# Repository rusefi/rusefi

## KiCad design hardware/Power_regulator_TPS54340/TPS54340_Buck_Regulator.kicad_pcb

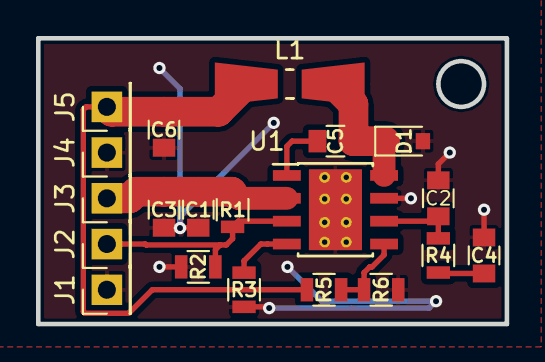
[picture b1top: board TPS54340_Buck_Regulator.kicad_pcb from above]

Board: 2 copper layers, 26.0 x 15.9 mm, 20 parts (0 on the bottom side), 10 nets.

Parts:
C1, C3: 2.2uF; C_0805
C2: 47pF; C_0805
C4: 5600pF; C_0805
C5: 0.1uF; C_0805
C6: 100uF; C_0805
D1: B560C; D_0805
J1, J2, J3, J4, J5: Conn_01x01; Pin_Header_Straight_1x01_Pitch2.54mm
L1: 5.6uH; Resistor_SMDuniversal_0805to1206_HandSoldering
R1: 365k; R_0805
R2: 86k6; R_0805
R3: 162k; R_0805
R4: 11k5; R_0805
R5: 31.6; R_0805
R6: 10.2; R_0805
U1: TPS54340; TI_SO-PowerPAD-8_ThermalVias

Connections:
/BOOT: C5.2, U1.1
/COMP: C2.1, R4.1, U1.6
/EN: J2.1, R1.1, R2.1, U1.3
/FB: R5.2, R6.1, U1.5
/RT/CLK: R3.1, U1.4
/SW: C5.1, D1.1, L1.1, U1.8
/VIN: C1.2, C3.2, J3.1, R1.2, U1.2
/VOUT: C6.1, J5.1, L1.2, R5.1
GND: C1.1, C2.2, C3.1, C4.2, C6.2, D1.2, J1.1, J4.1, R2.2, R3.2, R6.2, U1.7, U1.9
unnamed: C4.1, R4.2

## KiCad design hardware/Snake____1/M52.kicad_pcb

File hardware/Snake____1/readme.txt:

See http://rusefi.com/forum/viewtopic.php?f=3&t=1099 for details

By Snake____1

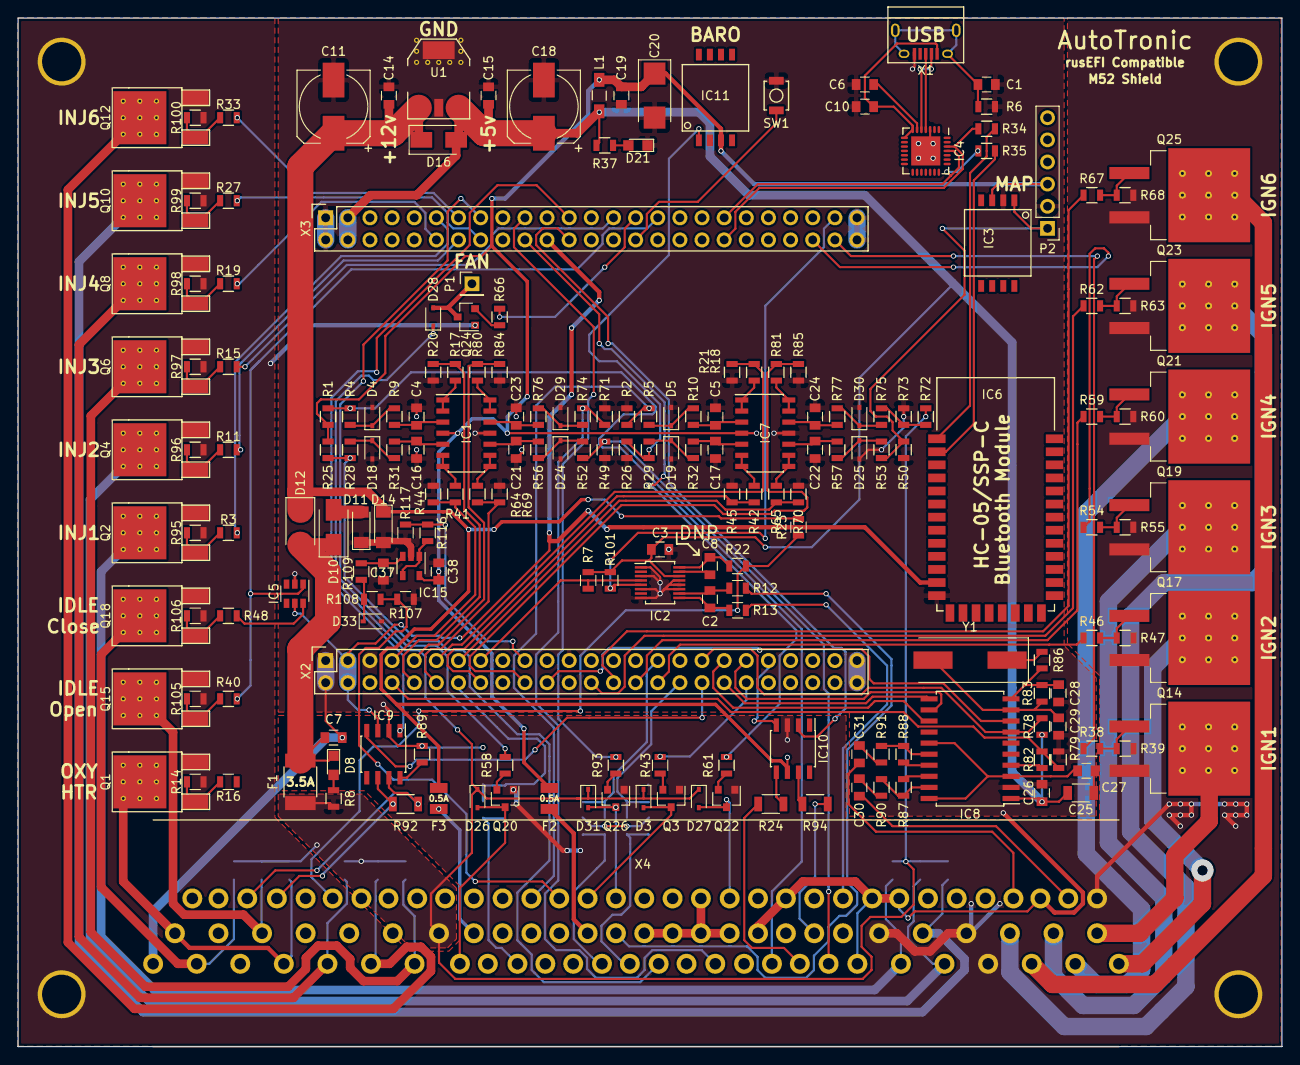
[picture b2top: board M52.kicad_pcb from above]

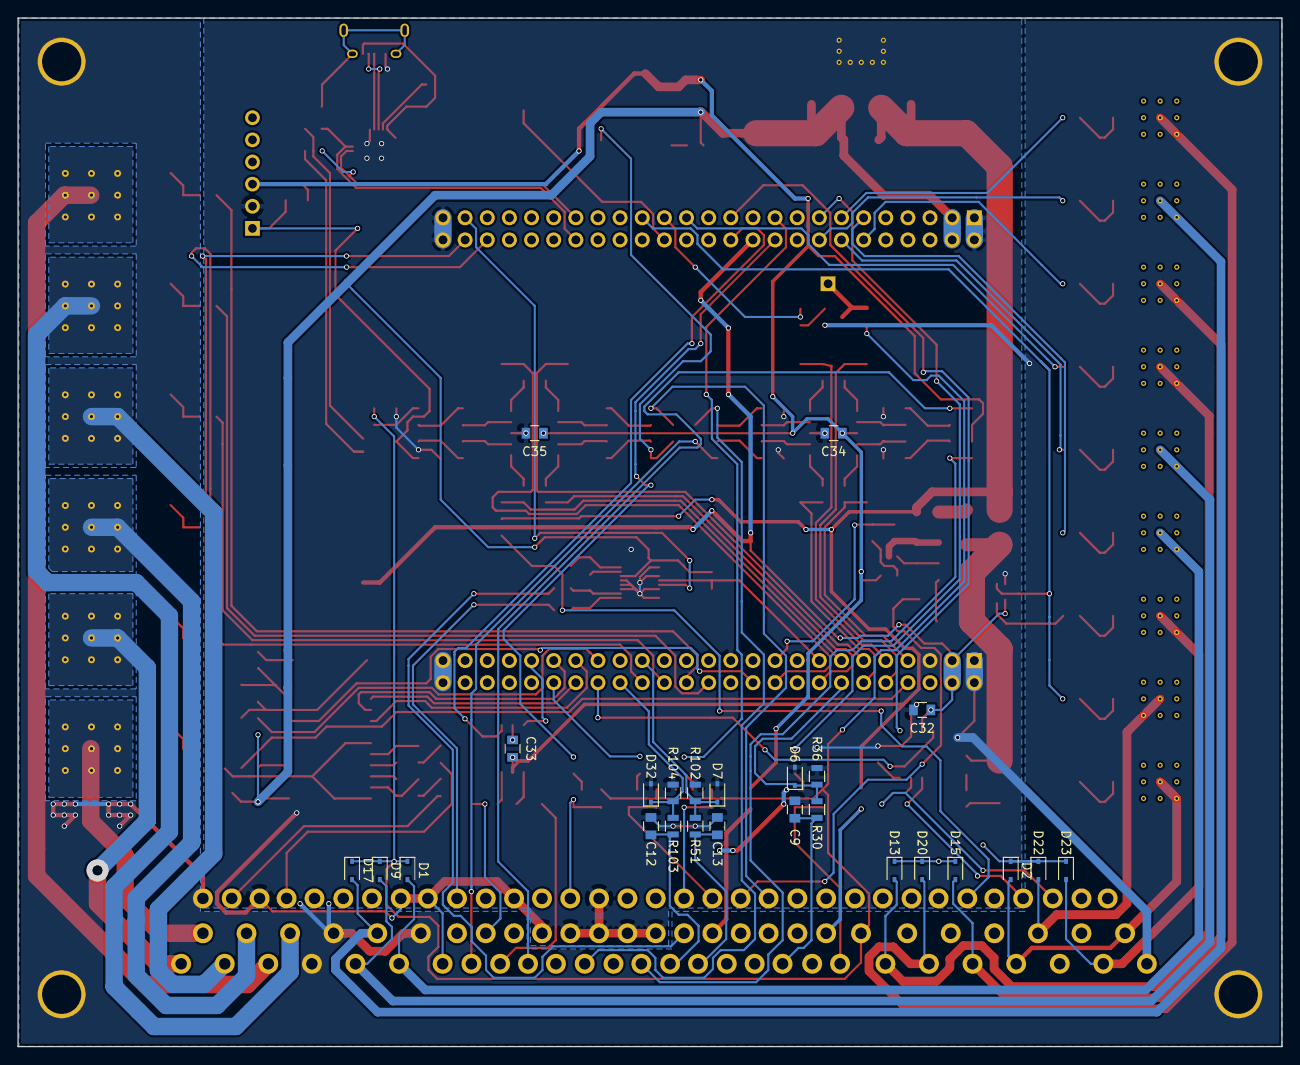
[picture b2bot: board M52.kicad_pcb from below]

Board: 2 copper layers, 145.0 x 118.0 mm, 226 parts (25 on the bottom side), 172 nets.

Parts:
C1, C3, C6, C10, C14, C15, C19, C26, C32, C33, C34, C35, C38: 100nF; C_0805
C2, C7, C8, C9: 1nF; C_0805
C4, C5, C12, C13, C16, C17, C21, C22, C23, C24, C37: 10nF; C_0805
C11, C18: 470uF; CP_Elec_8x10
C20: 10uF; CP_Tantalum_Case-C_EIA-6032-28_Reflow
C25: 4.7uF; C_1206
C27: 220nF; C_0805
C28, C29: 24pF; C_0805
C30, C31: 3.3nF; C_0805
D1, D2, D3, D9, D13, D15, D17, D20, D22, D23, D26, D27, D28, D31: LL4148; D_SOD-323
D4, D5, D18, D19, D24, D25, D29, D30, D33: 5.1v; D_SOD-323
D6, D7, D32: 3.3v; D_SOD-323
D8: RED; LED_0805
D10, D16: LL4007; D_SMA_Standard
D11: 12v; D_MiniMELF_Standard
D12: SS34; D_SMA_Standard
D14: 22v; D_MiniMELF_Standard
D21: GREEN; LED_0805
F1: 3.5A; R_1812
F2, F3: 500mA; Fuse_SMD1206_Reflow
IC1, IC7: MCP6004; SOIC-14_3.9x8.7mm_Pitch1.27mm
IC2: MAX9926; MSOP-16_3x4mm_Pitch0.5mm
IC3: MPXH6400; MPXH6300
IC4: CP2101; QFN-28-1EP_5x5mm_Pitch0.5mm
IC5: 74LVC2G04GW; SOT-23-6
IC6: HC-05
IC8: TPIC8101; SOIC-20W_7.5x12.8mm_Pitch1.27mm
IC9: SN65HVD230; SOIC-8_3.9x4.9mm_Pitch1.27mm
IC10: IX4424; SOIC-8_3.9x4.9mm_Pitch1.27mm
IC11: MPXH6115; MPXH6300
IC15: MCP6001; SOT-23-5
L1: 1uH; Choke_SMD_1206_Standard
P1: FAN; Pin_Header_Straight_1x01_Pitch2.54mm
P2: MAP; Pin_Header_Straight_1x06_Pitch2.54mm
Q1, Q2, Q4, Q6, Q8, Q10, Q12, Q15, Q18: IRLR3103
Q3, Q20, Q22, Q24, Q26: PN2222A; SOT-23
Q14, Q17, Q19, Q21, Q23, Q25: NGD8201; TO-263-3LeadThermal
R1, R25, R30, R51, R103: 2.7K; R_0805
R2, R26, R49, R50, R71, R107: 500K; R_0805
R3, R11, R15, R16, R19, R23, R27, R33, R34, R35, R36, R38, R40, R43, R46, R48, R54, R58, R59, R61, R62, R66, R67, R93, R102, R104: 1K; R_0805
R4, R5, R7, R8, R12, R13, R22, R28, R29, R37, R52, R53, R73, R74, R75, R79, R82, R89, R101, R108: 10K; R_0805
R6, R14, R39, R47, R55, R60, R63, R68, R95, R96, R97, R98, R99, R100, R105, R106: 100K; R_0805
R9, R10, R31, R32, R56, R57, R76, R77, R109: 100R; R_0805
R17, R18, R20, R21, R41, R42, R44, R45, R64, R65, R69, R70, R80, R81, R84, R85, R116, R117: 1.5K; R_0805
R24, R94: 22R; R_1206
R72: 50K; R_0805
R78: 5K; R_0805
R83: 2M; R_0805
R86: 820R; R_0805
R87, R88, R90, R91: 39K; R_0805
R92: 120R; R_1206
SW1: HRD_RST; SW_SPST_B3U-1000P
U1: LM340MP-5.0/NOPB; SOT-223
X1: USB_OTG; USB_Micro-B
X2, X3: CONN_02X25; Socket_Strip_Straight_2x25
X4: CONN_02X44; BOSCH-88pin
Y1: 8MHz; Crystal_SMD_HC49-SD

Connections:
5vOUT: F2.2, X4.44
12vOUT: F3.2, X4.48
+3V3: C32.1, IC5.5, IC6.12, IC9.3, X2.3, X2.4, X3.22
+5V: C3.2, C15.1, C18.1, C25.1, C26.1, D16.2, IC2.14, IC8.1, L1.1, R7.2, R37.2, R78.2, R101.2, U1.3, X3.3, X3.4
+5VA: C19.1, C20.1, C34.1, C35.1, C38.1, F2.1, IC1.4, IC3.3, IC7.4, IC11.3, IC15.5, L1.2, P2.3, R1.1, R25.1
+12P: D1.1, D2.1, D3.1, D9.1, D13.1, D15.1, D17.1, D20.1, D22.1, D23.1, D26.1, D27.1, D28.1, D31.1, F1.1, R8.1, R72.1, X4.49
+12V: C11.1, C14.1, C33.2, D12.1, D14.1, D16.1, F3.1, IC10.6, R23.1, U1.1
AC: D3.2, Q3.3, X4.74
ACprSW: C13.1, R51.1, X4.16
ACreq: C9.1, R30.1, X4.19
BARO: IC11.1, R26.1, R29.1
CAM+: R13.2, X4.65
CAM-: R12.2, X4.43
CANH: IC9.7, R92.1, X4.86
CANL: IC9.6, R92.2, X4.85
CLT: R1.2, R4.1, X4.10
CRK: R22.2, R23.2, X4.83
ECU: D31.2, Q26.3, X4.73
FAN: D28.2, P1.1, Q24.3
FP: D27.2, Q22.3, X4.69
GND: C1.1, C3.1, C4.2, C5.2, C6.2, C7.2, C9.2, C10.2, C11.2, C12.2, C13.2, C14.2, C15.2, C16.2, C17.2, C18.2, C19.2, C20.2, C21.2, C22.2, C23.2, C24.2, C25.2, C26.2, C27.2, C28.1, C29.1, C32.2, C34.2, C35.2, C37.2, C38.2, D4.2, D5.2, D6.2, D7.2, D11.1, D14.2, D18.2, D19.2, D21.1, D24.2, D25.2, D29.2, D30.2, D32.2, D33.2, IC1.11, IC2.1, IC2.3, IC2.6, IC2.8, IC2.11, IC2.12, IC2.13, IC3.2, IC4.3, IC4.29, IC5.2, IC6.13, IC7.11, IC8.2, IC9.2, IC11.2, IC15.2, P2.2, R2.2, R6.1, R20.2, R21.2, R26.2, R36.2, R44.2, R45.2, R49.2, R50.2, R69.2, R70.2, R71.2, R73.2, R79.1, R84.2, R85.2, R89.1, R102.2, R104.2, R107.2, R117.2, SW1.1, U1.2, U1.4, X1.5, X2.1, X2.2, X2.5, X2.23, X2.49, X2.50, X3.1, X3.2, X3.49, X3.50, X4.7, X4.28, X4.38, X4.39, X4.40, X4.41, X4.42, X4.58, X4.63, X4.64, X4.67, X4.70
GNDPWR: C33.1, IC10.3, Q1.3, Q2.3, Q3.1, Q4.3, Q6.3, Q8.3, Q10.3, Q12.3, Q14.3, Q15.3, Q17.3, Q18.3, Q19.3, Q20.1, Q21.3, Q22.1, Q23.3, Q24.1, Q25.3, Q26.1, R14.2, R39.2, R47.2, R55.2, R60.2, R63.2, R68.2, R95.2, R96.2, R97.2, R98.2, R99.2, R100.2, R105.2, R106.2, X4.4, X4.32, X4.34, X4.56
IAT: R25.2, R28.1, X4.14
IDLc: D23.2, Q18.2, X4.27
IDLo: D22.2, Q15.2, X4.53
IGN1: Q14.2, X4.29
IGN2: Q17.2, X4.1
IGN3: Q19.2, X4.30
IGN4: Q21.2, X4.2
IGN5: Q23.2, X4.31
IGN6: Q25.2, X4.3
INJ1: D1.2, Q2.2, X4.6
INJ2: D9.2, Q4.2, X4.5
INJ3: D13.2, Q6.2, X4.22
INJ4: D15.2, Q8.2, X4.24
INJ5: D17.2, Q10.2, X4.33
INJ6: D20.2, Q12.2, X4.23
KNK1: C30.2, X4.57
KNK2: C31.1, X4.59
MAF: R49.1, R52.1, X4.8
MAP: IC3.1, P2.1, R50.1, R53.1
unnamed: C1.2, R6.2, X1.6
unnamed: C2.1, IC2.10, R12.1
unnamed: C2.2, IC2.9, R13.1
unnamed: C4.1, IC1.3, R9.2
unnamed: C5.1, IC7.3, R10.2
unnamed: C6.1, IC4.6
unnamed: C7.1, D8.1, D10.1, D12.2, F1.2
unnamed: C8.1, IC2.16, R22.1
unnamed: C8.2, IC2.15
unnamed: C10.1, IC4.7, IC4.8, X1.1
unnamed: C16.1, IC1.5, R31.2
unnamed: C17.1, IC7.5, R32.2
unnamed: C21.1, IC1.10, R56.2
unnamed: C22.1, IC7.10, R57.2
unnamed: C23.1, IC1.12, R76.2
unnamed: C24.1, IC7.12, R77.2
unnamed: C27.1, IC8.3, IC8.15, IC8.20
unnamed: C28.2, IC8.10, R83.1, R86.1
unnamed: C29.2, IC8.9, R83.2, Y1.2
unnamed: C30.1, R90.2
unnamed: C31.2, R91.1
unnamed: C37.1, IC15.3, R109.2
unnamed: D4.1, R4.2, R9.1
unnamed: D5.1, R5.2, R10.1
unnamed: D8.2, R8.2
unnamed: D10.2, D11.2
unnamed: D18.1, R28.2, R31.1
unnamed: D19.1, R29.2, R32.1
unnamed: D21.2, R37.1
unnamed: D24.1, R52.2, R56.1
unnamed: D25.1, R53.2, R57.1
unnamed: D29.1, R74.2, R76.1
unnamed: D30.1, R75.2, R77.1
unnamed: D33.1, R108.2, R109.1
unnamed: IC1.1, IC1.2, R17.1
unnamed: IC1.6, IC1.7, R41.1
unnamed: IC1.8, IC1.9, R64.1
unnamed: IC1.13, IC1.14, R80.1
unnamed: IC4.4, X1.3
unnamed: IC4.5, X1.2
unnamed: IC5.6, R48.1
unnamed: IC6.1, R34.2
unnamed: IC6.2, R35.1
unnamed: IC7.1, IC7.2, R18.1
unnamed: IC7.6, IC7.7, R42.1
unnamed: IC7.8, IC7.9, R65.1
unnamed: IC7.13, IC7.14, R81.1
unnamed: IC8.4, R82.1
unnamed: IC8.16, R88.1, R91.2
unnamed: IC8.17, R88.2
unnamed: IC8.18, R87.1
unnamed: IC8.19, R87.2, R90.1
unnamed: IC9.8, R89.2
unnamed: IC10.5, R24.1
unnamed: IC10.7, R94.1
unnamed: IC15.1, IC15.4, R116.1
unnamed: Q1.1, R14.1, R16.2
unnamed: Q2.1, R3.2, R95.1
unnamed: Q3.2, R43.1
unnamed: Q4.1, R11.2, R96.1
unnamed: Q6.1, R15.2, R97.1
unnamed: Q8.1, R19.2, R98.1
unnamed: Q10.1, R27.2, R99.1
unnamed: Q12.1, R33.2, R100.1
unnamed: Q14.1, R38.2, R39.1
unnamed: Q15.1, R40.2, R105.1
unnamed: Q17.1, R46.2, R47.1
unnamed: Q18.1, R48.2, R106.1
unnamed: Q19.1, R54.2, R55.1
unnamed: Q20.2, R58.1
unnamed: Q21.1, R59.2, R60.1
unnamed: Q22.2, R61.1
unnamed: Q23.1, R62.2, R63.1
unnamed: Q24.2, R66.1
unnamed: Q25.1, R67.2, R68.1
unnamed: Q26.2, R93.1
unnamed: R72.2, R73.1, R75.1
unnamed: R86.2, Y1.1
OXY1: R107.1, R108.1, X4.75
OXY2: R2.1, R5.1, X4.76
OXYHTR: D2.2, Q1.2, X4.25, X4.55
PA0: R64.2, R69.1, X2.12
PA1: R18.2, R21.1, X2.11
PA2: D6.1, R30.2, R36.1, X2.14
PA3: R65.2, R70.1, X2.13
PA4: R42.2, R45.1, X2.16
PA5: IC2.4, R7.1, X2.15
PB0: IC8.8, X2.22
PB6: IC9.1, X3.23
PB7: IC10.2, X3.24
PB8: R93.2, X3.19
PB9: R61.2, X3.20
PB10: D32.1, R103.2, R104.1, X2.34
PB11: IC8.7, R78.1, X2.35
PB12: IC9.4, X2.36
PB13: IC8.13, X2.37
PB14: IC8.11, X2.38
PB15: IC8.12, X2.39
PC0: R79.2, R82.2, X2.8
PC1: R41.2, R44.1, X2.7
PC2: R17.2, R20.1, X2.10
PC3: R80.2, R84.1, X2.9
PC4: R81.2, R85.1, X2.20
PC5: R116.2, R117.1, X2.19
PC6: IC2.5, R101.1, X3.47
PC7: R38.1, X3.48
PC9: R54.1, X3.46
PC10: IC4.25, R35.2, X3.37
PC11: IC4.26, R34.1, X3.38
PC13: R19.1, X3.12
PD3: IC5.1, R40.1, X3.31
PD5: R66.2, X3.29
PD6: SW1.2, X3.30
PD7: R15.1, X3.27
PD8: R43.2, X2.40
PD9: IC10.4, X2.41
PE2: R58.2, X3.15
PE3: R27.1, X3.16
PE4: R33.1, X3.13
PE5: R11.1, X3.14
PE6: R3.1, X3.11
PE8: R62.1, X2.26
PE10: R67.1, X2.28
PE12: R59.1, X2.30
PE13: D7.1, R51.2, R102.1, X2.31
PE14: R46.1, X2.32
RPM: R94.2, X4.36
TI: R24.2, X4.9
TPS: R71.1, R74.1, X4.12
VANOS: D26.2, Q20.3, X4.21
VSS: C12.1, R103.1, X4.15

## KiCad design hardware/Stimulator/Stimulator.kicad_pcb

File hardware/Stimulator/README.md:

Stimulator
==========

Rusefi Stimulator

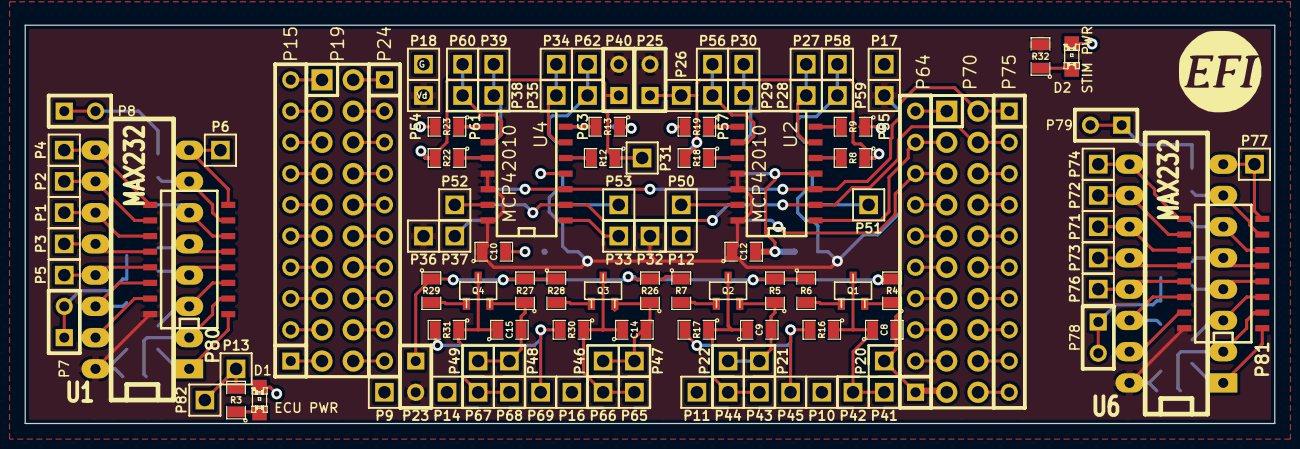
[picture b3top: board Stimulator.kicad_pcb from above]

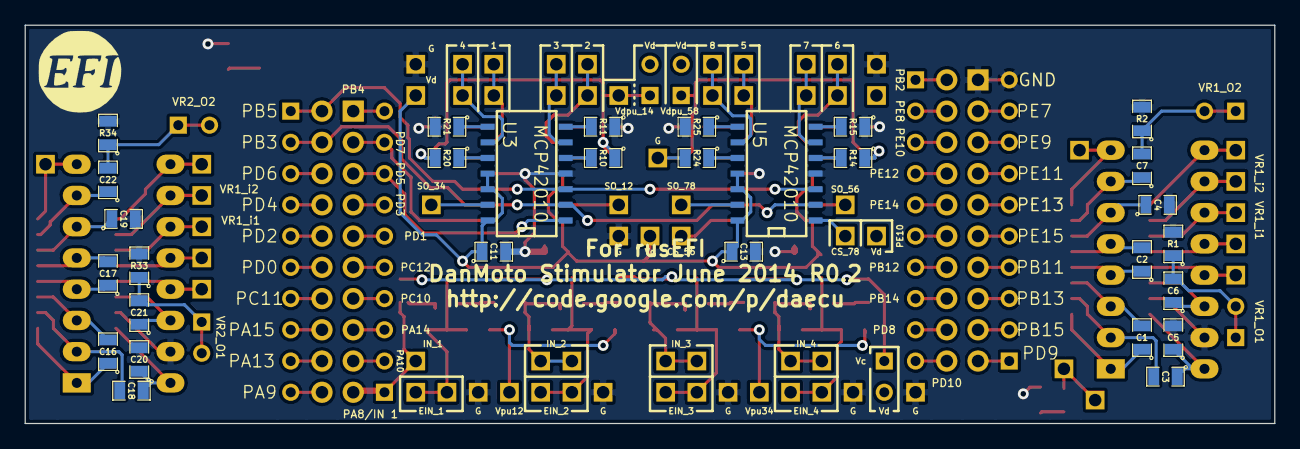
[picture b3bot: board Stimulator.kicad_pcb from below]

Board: 2 copper layers, 101.6 x 32.4 mm, 150 parts (30 on the bottom side), 122 nets.

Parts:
C1, C2, C3, C4, C5, C6, C7, C16, C17, C18, C19, C20, C21, C22: 1uF; SM0805
C8, C9, C14, C15: 100 pF; SM0805
C10, C11, C12, C13: 0.1uF; SM0805
D1: ECU PWR; LED-0805
D2: STIM PWR; LED-0805
P1, P2, P3, P4, P5, P6, P9, P10, P11, P12, P13, P14, P16, P17, P18, P20, P21, P22, P26, P27, P28, P29, P30, P31, P32, P33, P34, P35, P36, P37, P38, P39, P41, P42, P43, P44, P45, P46, P47, P48, P49, P50, P51, P52, P53, P54, P55, P56, P57, P58, P59, P60, P61, P62, P63, P65, P66, P67, P68, P69, P71, P72, P73, P74, P76, P77, P82: CONN_1; PIN_ARRAY_1
P7, P8, P23, P25, P40, P78, P79: TEST; SIL-2
P15, P24, P64, P75: CONN_10; SIL-10
P19, P70: CONN_10X2; Pin_Header_Straight_2x10
P80, P81: DIL16; SO16N
Q1, Q2, Q3, Q4: 2N7002; sot23
R1, R2, R4, R5, R6, R7, R16, R17, R26, R27, R28, R29, R30, R31, R33, R34: 10k; SM0805
R3, R32: 700R; SM0805
R8, R9, R10, R11, R12, R13, R14, R15, R18, R19, R20, R21, R22, R23, R24, R25: 0; SM0805
U1, U6: MAX232; DIP-16__300_ELL
U2, U3, U4, U5: MCP42010; SO14N

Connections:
/CS_12: P64.9, P70.3, U2.1
/CS_34: P64.8, P70.5, U3.1
/CS_56: P33.1, U4.1
/CS_78: P37.1, U5.1
/EIN_1: C8.1, P41.1, P42.1, Q1.2, R16.1
/EIN_2: C9.1, P43.1, P44.1, Q2.2, R17.1
/EIN_3: C14.1, P65.1, P66.1, Q3.2, R30.1
/EIN_4: C15.1, P67.1, P68.1, Q4.2, R31.1
/IN_1: C8.2, P20.1, P64.1, P70.19, Q1.3, R4.1
/IN_2: C9.2, P21.1, P22.1, Q2.3, R5.1
/IN_3: C14.2, P46.1, P47.1, Q3.3, R26.1
/IN_4: C15.2, P48.1, P49.1, Q4.3, R27.1
/MISO: P64.10, P70.1
/MOSI: P70.2, P75.1, U2.3, U3.3, U4.3, U5.3
/OUT1: P27.1, P28.1, U2.6
/OUT2: P56.1, P57.1, U2.9
/OUT3: P29.1, P30.1, U3.6
/OUT4: P58.1, P59.1, U3.9
/OUT5: P34.1, P35.1, U4.6
/OUT6: P60.1, P61.1, U4.9
/OUT7: P38.1, P39.1, U5.6
/OUT8: P62.1, P63.1, U5.9
/SCK: P70.4, P75.2, U2.2, U3.2, U4.2, U5.2
/U1-01: C1.1, P80.1, U1.1
/U1-02: C3.2, P80.2, U1.2
/U1-03: C1.2, P80.3, U1.3
/U1-04: C2.1, P80.4, U1.4
/U1-05: C2.2, P80.5, U1.5
/U1-06: C4.1, P80.6, U1.6
/U1-07: C7.1, P80.7, U1.7
/U1-08: P6.1, P80.8, U1.8
/U1-09: P4.1, P80.9, U1.9
/U1-12: P3.1, P80.12, U1.12
/U1-13: P5.1, P80.13, U1.13
/U1-14: C6.1, P80.14, U1.14
/U6-01: C16.1, P81.1, U6.1
/U6-02: C18.2, P81.2, U6.2
/U6-03: C16.2, P81.3, U6.3
/U6-04: C17.1, P81.4, U6.4
/U6-05: C17.2, P81.5, U6.5
/U6-06: C19.1, P81.6, U6.6
/U6-07: C22.1, P81.7, U6.7
/U6-08: P77.1, P81.8, U6.8
/U6-09: P74.1, P81.9, U6.9
/U6-12: P73.1, P81.12, U6.12
/U6-13: P76.1, P81.13, U6.13
/U6-14: C21.1, P81.14, U6.14
/VR1-O1: C6.2, P7.1, P7.2, R1.1
/VR1-O2: C7.2, P8.1, P8.2, R2.1
/VR1_i1: P1.1, P80.11, U1.11
/VR1_i2: P2.1, P80.10, U1.10
/VR2-O1: C21.2, P78.1, P78.2, R33.1
/VR2-O2: C22.2, P79.1, P79.2, R34.1
/VR2_i1: P71.1, P81.11, U6.11
/VR2_i2: P72.1, P81.10, U6.10
/Vc: P23.1, R4.2, R5.2, R6.1, R7.1, R26.2, R27.2, R28.1, R29.1
/Vd: C3.1, C5.1, C10.1, C11.1, C12.1, C13.1, C18.1, C20.1, P23.2, P25.2, P32.1, P36.1, P40.2, P54.1, P55.1, P80.16, P81.16, R32.2, U1.16, U2.11, U2.12, U2.14, U3.11, U3.12, U3.14, U4.11, U4.12, U4.14, U5.11, U5.12, U5.14, U6.16
/Vdpu_14: P25.1, P26.1, R8.1, R10.1, R18.2, R20.2
/Vdpu_58: P31.1, P40.1, R12.1, R14.1, R22.2, R24.2
/Vipu12: P45.1, R16.2, R17.2
/Vipu34: P69.1, R30.2, R31.2
GND: C4.2, C5.2, C10.2, C11.2, C12.2, C13.2, C19.2, C20.2, D1.2, D2.2, P9.1, P10.1, P11.1, P12.1, P14.1, P15.10, P16.1, P17.1, P18.1, P19.1, P80.15, P81.15, R1.2, R2.2, R9.1, R11.1, R13.1, R15.1, R19.2, R21.2, R23.2, R25.2, R33.2, R34.2, U1.15, U2.4, U3.4, U4.4, U5.4, U6.15
unnamed: P70.6, P75.3
unnamed: P70.20, P75.10
unnamed: P64.2, P70.17
unnamed: P64.3, P70.15
unnamed: P64.4, P70.13
unnamed: P64.5, P70.11
unnamed: P64.6, P70.9
unnamed: P64.7, P70.7
unnamed: P70.18, P75.9
unnamed: P70.8, P75.4
unnamed: P70.10, P75.5
unnamed: P70.12, P75.6
unnamed: P70.14, P75.7
unnamed: P70.16, P75.8
unnamed: P15.5, P19.11
unnamed: P19.4, P24.2
unnamed: P19.6, P24.3
unnamed: P19.8, P24.4
unnamed: P19.10, P24.5
unnamed: P19.12, P24.6
unnamed: P19.14, P24.7
unnamed: P19.16, P24.8
unnamed: P19.18, P24.9
unnamed: P19.20, P24.10
unnamed: P15.1, P19.19
unnamed: P15.2, P19.17
unnamed: P15.3, P19.15
unnamed: P15.4, P19.13
unnamed: P15.6, P19.9
unnamed: P15.7, P19.7
unnamed: P15.8, P19.5
unnamed: P15.9, P19.3
unnamed: P19.2, P24.1
unnamed: R14.2, U5.5
unnamed: R15.2, U5.7
unnamed: R25.1, U5.8
unnamed: R24.1, U5.10
unnamed: P50.1, U2.13
unnamed: P52.1, U4.13
unnamed: P51.1, U3.13
unnamed: P53.1, U5.13
unnamed: P13.1, P82.1, R3.2
unnamed: D2.1, R32.1
unnamed: D1.1, R3.1
unnamed: R8.2, U2.5
unnamed: R9.2, U2.7
unnamed: R19.1, U2.8
unnamed: R18.1, U2.10
unnamed: R10.2, U3.5
unnamed: Q3.1, R28.2
unnamed: Q2.1, R7.2
unnamed: Q4.1, R29.2
unnamed: R11.2, U3.7
unnamed: R21.1, U3.8
unnamed: R20.1, U3.10
unnamed: R12.2, U4.5
unnamed: R13.2, U4.7
unnamed: R23.1, U4.8
unnamed: R22.1, U4.10
unnamed: Q1.1, R6.2

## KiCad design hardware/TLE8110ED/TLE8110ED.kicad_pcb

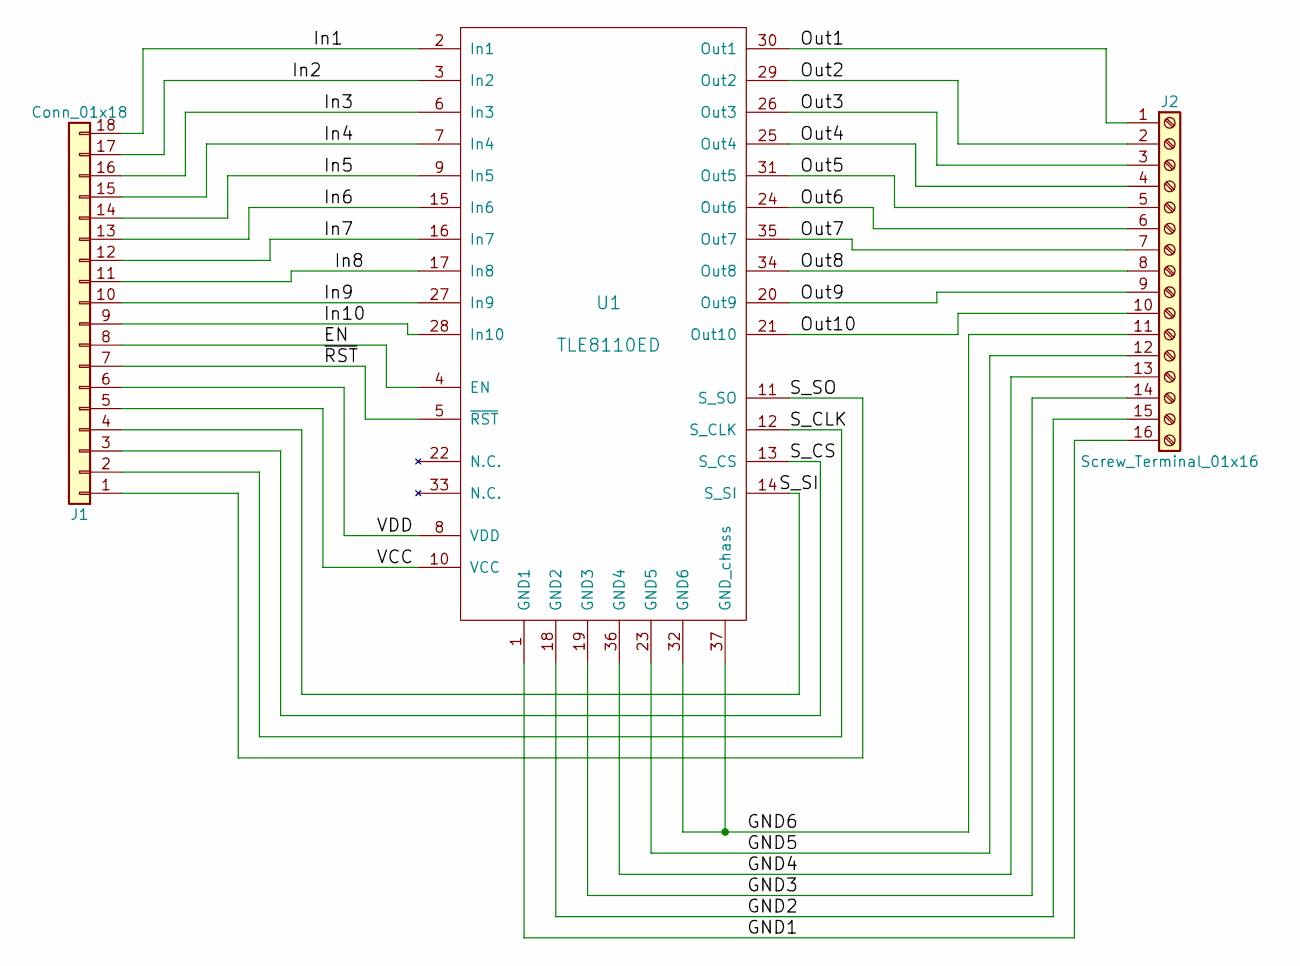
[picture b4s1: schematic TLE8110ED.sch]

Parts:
J1: Conn_01x18; Pin_Header_Straight_1x18_Pitch2.54mm
J2: Screw_Terminal_01x16; TerminalBlock_Pheonix_PT-3.5mm_16pol
U1: TLE8110ED; PG-DSO-36-72

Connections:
/EN: J1.8, U1.4 (EN)
/GND1: J2.16, U1.1 (GND1)
/GND2: J2.15, U1.18 (GND2)
/GND3: J2.14, U1.19 (GND3)
/GND4: J2.13, U1.36 (GND4)
/GND5: J2.12, U1.23 (GND5)
/GND6: J2.11, U1.32 (GND6), U1.37 (GND_chass)
/In1: J1.18, U1.2 (In1)
/In2: J1.17, U1.3 (In2)
/In3: J1.16, U1.6 (In3)
/In4: J1.15, U1.7 (In4)
/In5: J1.14, U1.9 (In5)
/In6: J1.13, U1.15 (In6)
/In7: J1.12, U1.16 (In7)
/In8: J1.11, U1.17 (In8)
/In9: J1.10, U1.27 (In9)
/In10: J1.9, U1.28 (In10)
/Out1: J2.1, U1.30 (Out1)
/Out2: J2.2, U1.29 (Out2)
/Out3: J2.3, U1.26 (Out3)
/Out4: J2.4, U1.25 (Out4)
/Out5: J2.5, U1.31 (Out5)
/Out6: J2.6, U1.24 (Out6)
/Out7: J2.7, U1.35 (Out7)
/Out8: J2.8, U1.34 (Out8)
/Out9: J2.9, U1.20 (Out9)
/Out10: J2.10, U1.21 (Out10)
/S_CLK: J1.2, U1.12 (S_CLK)
/S_CS: J1.3, U1.13 (S_CS)
/S_SO: J1.1, U1.11 (S_SO)
/VCC: J1.5, U1.10 (VCC)
/VDD: J1.6, U1.8 (VDD)
/~RST: J1.7, U1.5 (~RST)
unnamed: J1.4, U1.14 (S_SI)

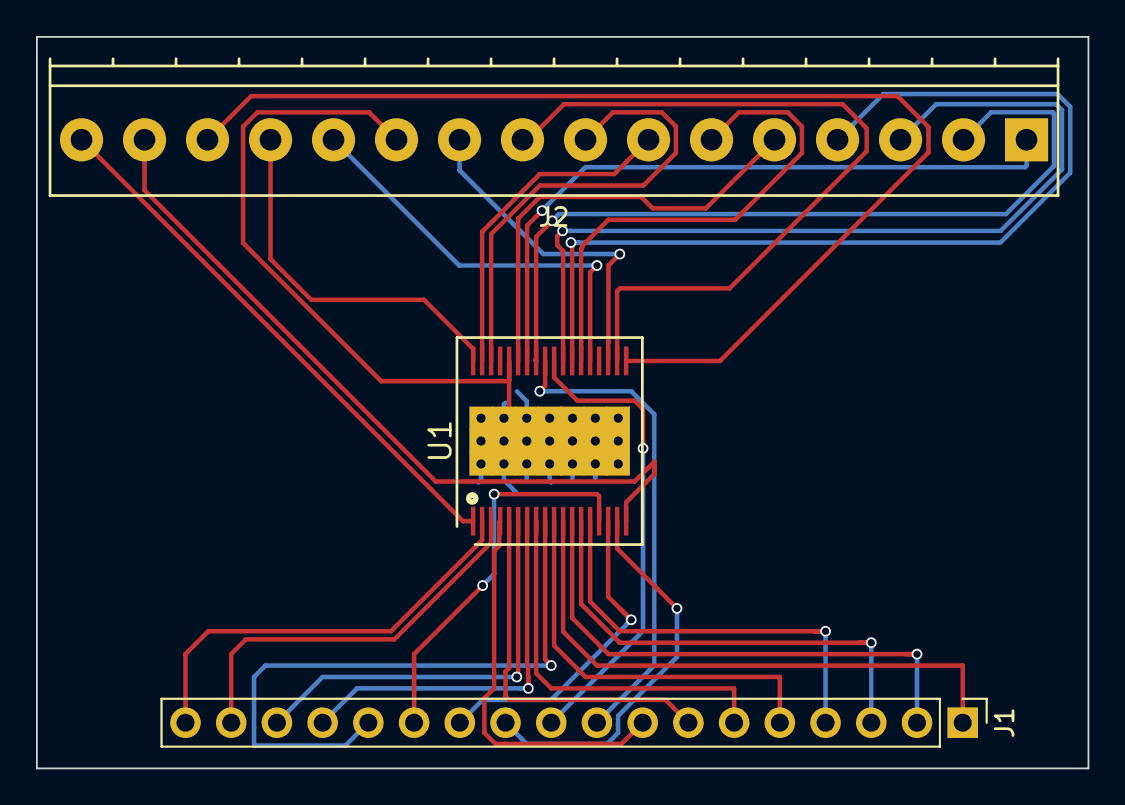
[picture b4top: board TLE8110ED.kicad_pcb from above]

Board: 2 copper layers, 58.4 x 40.6 mm, 3 parts (0 on the bottom side), 34 nets.

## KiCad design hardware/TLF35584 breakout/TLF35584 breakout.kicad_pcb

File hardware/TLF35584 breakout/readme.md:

Kidcad 5.0.2 files for TLF35584 power supply chip

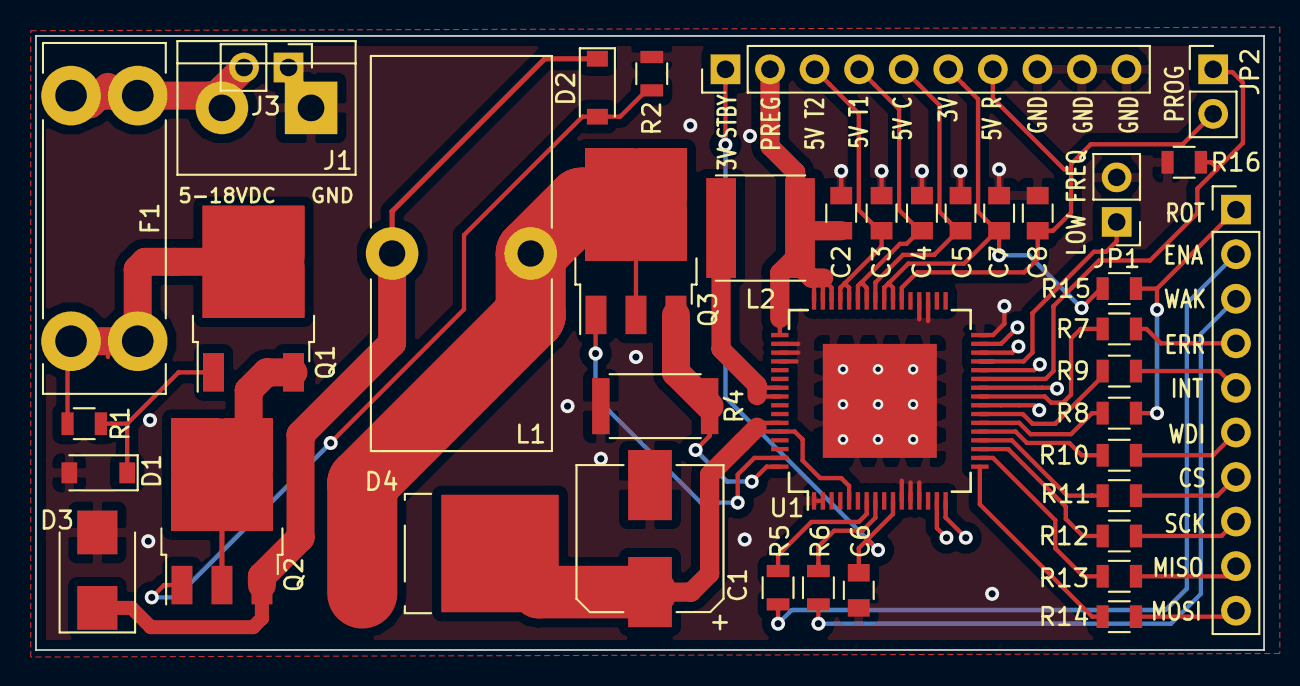
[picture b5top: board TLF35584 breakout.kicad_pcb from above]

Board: 2 copper layers, 70.0 x 35.0 mm, 40 parts (0 on the bottom side), 41 nets.

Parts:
C1: 100uF/50V; CP_Elec_8x10.5
C2, C5, C7: 22uF/16V; C_0805
C3, C4, C6, C8: 4.7uF/16V; C_0805
D1, D2: BZT52C18; D_SOD-123
D3: SMBJ24A; D_SMB
D4: MBRD835LT4G; DPAK_Diode
F1: 5A Fuse; Fuseholder_blade
J1: POWER_IN; TerminalBlock_bornier-2_P5.08mm
J2: SIGNALS; Pin_Header_Straight_1x10_Pitch2.54mm
J3: POWER_IN; Pin_Header_Straight_1x02_Pitch2.54mm
J4: POWER_OUT; Pin_Header_Straight_1x10_Pitch2.54mm
JP1: FRE; Pin_Header_Straight_1x02_Pitch2.54mm
JP2: MPS; Pin_Header_Straight_1x02_Pitch2.54mm
L1: 22uH/8A; L_Toroid_Vertical_L22.4mm_W10.2mm_P7.90mm_Vishay_TJ4
L2: 4.7uH/3A; 6.0X6.0X3.0
Q1: DN2625K4; TO-252-2
Q2: NTD2955T4G; TO-252-3_TabPin2
Q3: NTD20N06LT4G; TO-252-3_TabPin2
R1: 100K; R_0805
R2: 39K; R_0805
R4: 0.03R; R_2512
R5, R6, R7, R8, R9, R10, R11, R12, R13, R14: 1K; R_0805
R15, R16: 10K; R_0805
U1: TLF35584QKVS2; LQFP-64-1EP_10x10mm_Pitch0.5mm

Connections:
/3.3V_STBY: C6.1, J4.1, U1.10
/3.3V_UC: C7.1, J4.6, R15.1, U1.39, U1.40
/5V_COMMS: C5.1, J4.5, U1.41
/5V_REF: C8.1, J4.7, JP2.2, U1.38
/5V_TRACKER1: C3.1, J4.3, U1.44, U1.45
/5V_TRACKER2: C4.1, J4.4, U1.42, U1.43
/12V_BAT: F1.2, J1.2, J3.2
/ENABLE: J2.2, R5.1
/ERR: J2.4, R7.2
/INT: J2.5, R9.2
/ROT: J2.1, R8.2, R15.2
/SPI_CS: J2.7, R11.2
/SPI_MISO: J2.9, R13.2
/SPI_MOSI: J2.10, R14.2
/SPI_SCK: J2.8, R12.2
/VST: C1.1, D4.1, U1.5, U1.59, U1.60
/V_PREREG: C2.2, J4.2, L2.2, U1.46, U1.47, U1.48, U1.49
/WAKE: J2.3, R6.1
/WDI: J2.6, R10.2
GND: C1.2, C2.1, C3.2, C4.2, C5.2, C6.2, C7.2, C8.2, D1.2, D3.2, J1.1, J3.1, J4.8, J4.9, J4.10, JP1.2, R2.2, R4.1, R16.2, U1.1, U1.2, U1.11, U1.12, U1.13, U1.28, U1.32, U1.35, U1.36, U1.50, U1.51, U1.52, U1.65
unnamed: D1.1, Q1.1, R1.2
unnamed: D2.1, D3.1, L1.2, Q2.3
unnamed: D2.2, Q2.1, R2.1
unnamed: D4.2, L1.1, Q3.2
unnamed: F1.1, Q1.2, R1.1
unnamed: JP1.1, U1.29
unnamed: JP2.1, R16.1, U1.27
unnamed: L2.1, U1.55, U1.56
unnamed: Q1.3, Q2.2
unnamed: Q3.1, U1.63
unnamed: Q3.3, R4.2, U1.64
unnamed: R5.2, U1.7
unnamed: R6.2, U1.8
unnamed: R7.1, U1.25
unnamed: R8.1, U1.22
unnamed: R9.1, U1.23
unnamed: R10.1, U1.21
unnamed: R11.1, U1.20
unnamed: R12.1, U1.19
unnamed: R13.1, U1.18
unnamed: R14.1, U1.17

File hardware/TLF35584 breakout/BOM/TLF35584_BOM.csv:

References,Quantity,Value,Footprint,Part Manufacturer,Part #,Specs
"C2, C5, C7",3,22uF/16V,C_0805,Samsung Electro-Mechanics,CL21A226MOQNNNE,X5R/X7R low ESR 200 mohm max
"C3, C4, C6, C8",4,4.7uF/16V,C_0805,Samsung Electro-Mechanics,CL21A475KOFNNNE,X5R/X7R low ESR 200 mohm max
C1,1,100uF/50V,CP_Elec_8x10.5,Semtech,CS1H101M-CRF10,Aluminium electrolytic cap
"R5, R6, R7, R8, R9, R10, R11, R12, R13, R14",10,1K,R_0805,,,
"R15, R16",2,10K,R_0805,,,
R1,1,100K,R_0805,,,
R2,1,39K,R_0805,,,
R4,1,0.03R,R_2512,FORT,CUM2512-24FR030,Current sense resistor (min 2W)
L1,1,22uH/8A,L_Toroid_Vertical_L22.4mm_W10.2mm_P7.90mm_Vishay_TJ4,,,Radial inductor
L2,1,4.7uH/3A,6.0X6.0X3.0,Bourns,SRN5040TA-4R7M,(Shun Xiang Nuo Elec - SMNR6028-4R7MT)
"D1, D2",2,BZT52C18,D_SOD-123,Diodes Incorporated,BZT52C18-7-F,18V Zener diode
D4,1,MBRD835LT4G,DPAK_Diode,ON Semicon,MBRD835LT4G,Schottky diode Min 8V/8A
D3,1,SMBJ24A,D_SMB,(MDD) Jiangsu Yutai Elec,SMBJ24A,24V TVS diode
U1,1,TLF35584QKVS2,LQFP-64-1EP_10x10mm_Pitch0.5mm,,,
F1,1,5A Fuse,Fuseholder_blade,Keystone Electronics,3557-15,or unbranded ebay equivalent
JP1,1,FRE,Pin_Header_Straight_1x02_Pitch2.54mm,,,
JP2,1,MPS,Pin_Header_Straight_1x02_Pitch2.54mm,,,
G***,1,rusEFI_logo_25mm,rusEFI_logo_25mm,,,
Q1,1,DN2625K4,TO-252-2,Microchip,DN2625K4-G,N channel MOSFET (min 5A/200V)(STMicroelectronics - STD13NM60N)
Q3,1,NTD20N06LT4G,TO-252-3_TabPin2,ON Semicon,NTD20N06LT4G,N channel MOSFET (min 8A/50V)
Q2,1,NTD2955T4G,TO-252-3_TabPin2,ON Semicon,NTD2955T4G,P channel MOSFET (min 5A/25V)
J3,1,POWER_IN,Pin_Header_Straight_1x02_Pitch2.54mm,,,
J2,1,SIGNALS,Pin_Header_Straight_1x10_Pitch2.54mm,,,
J4,1,POWER_OUT,Pin_Header_Straight_1x10_Pitch2.54mm,,,
J1,1,POWER_IN,TerminalBlock_bornier-2_P5.08mm,,,or unbranded ebay equivalent

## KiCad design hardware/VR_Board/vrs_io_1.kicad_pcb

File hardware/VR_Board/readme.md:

Variable Reluctance conditioner board VR MAX9926

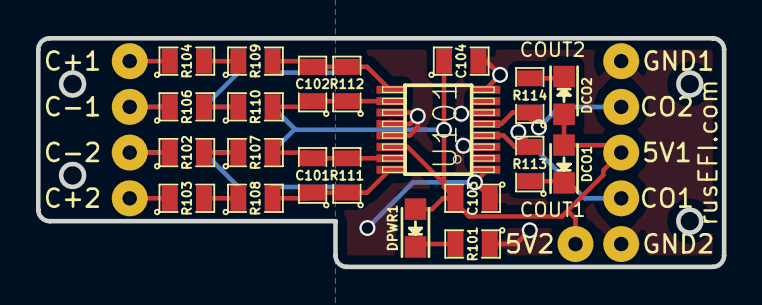
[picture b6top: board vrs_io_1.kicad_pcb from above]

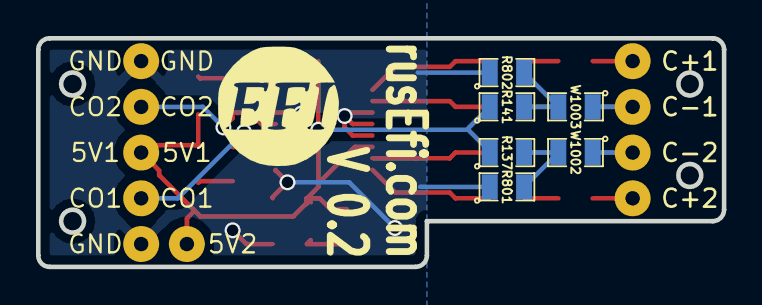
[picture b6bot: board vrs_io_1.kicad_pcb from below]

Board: 2 copper layers, 38.1 x 12.7 mm, 38 parts (11 on the bottom side), 21 nets.

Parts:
5V1, 5V2: CONN_01X01; SolderWirePad_single_0-8mmDrill
C101, C102: 1000pF; SM0805
C103: 10uF; SM0805
C104: 0.1uF; SM0805
C+1, C+2: CONN_01X01; SolderWirePad_single_0-8mmDrill
C-1, C-2: CONN_01X01; SolderWirePad_single_0-8mmDrill
CO1, CO2: CONN_01X01; SolderWirePad_single_0-8mmDrill
DCO1, DCO2: LED-red; LED_0805
DPWR1: LED-red; LED_0805
G?: LOGO; LOGO_F
GND1, GND2: CONN_01X01; SolderWirePad_single_0-8mmDrill
R101, R113, R114: 10k; SM0805
R102, R103, R104, R106, R107, R108, R109, R110, R111, R112: 5k; SM0805
R137, R141: 1K; SM0805
R801, R802: pdwn; SM0805
U101: MAX9926/9927; maxim-10-QSOP16
W1002, W1003: JMP; SM0805

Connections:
/5V: 5V1.1, 5V2.1, C103.2, C104.1, DCO1.2, DCO2.2, DPWR1.2, R137.1, R141.1, U101.14
/CAM+: C+1.1, R104.1
/CAM-: C-1.1, R106.1, W1003.1
/CRK2+: C+2.1, R103.1
/CRK2-: C-2.1, R102.1, W1002.1
/Cout1: CO1.1, R113.2, U101.4
/Cout2: CO2.1, R114.1, U101.5
GND: C103.1, C104.2, GND1.1, GND2.1, R101.1, R801.1, R802.1, U101.1, U101.3, U101.6, U101.8, U101.11, U101.12, U101.13
unnamed: C101.1, R108.2, R111.1, U101.16
unnamed: C101.2, R107.2, R111.2, U101.15
unnamed: C102.1, R110.2, R112.1, U101.10
unnamed: C102.2, R109.2, R112.2, U101.9
unnamed: DCO1.1, R113.1
unnamed: DCO2.1, R114.2
unnamed: DPWR1.1, R101.2
unnamed: R102.2, R107.1
unnamed: R103.2, R108.1
unnamed: R104.2, R109.1
unnamed: R106.2, R110.1
unnamed: R137.2, R801.2, W1002.2
unnamed: R141.2, R802.2, W1003.2

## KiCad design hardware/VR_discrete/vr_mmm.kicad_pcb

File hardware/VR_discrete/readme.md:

Huh, what do we have here?

https://github.com/mck1117/vr-interface would be much more proven

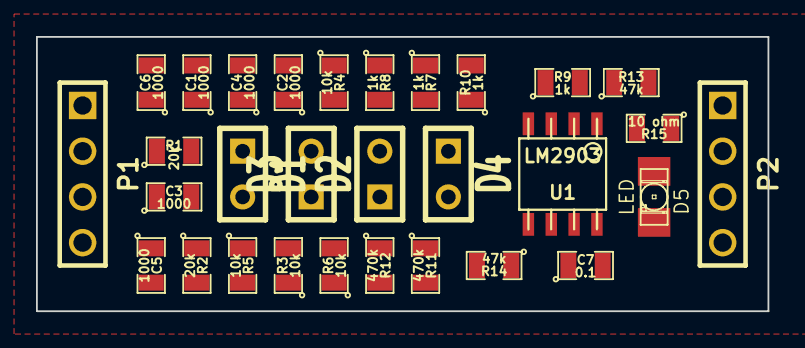
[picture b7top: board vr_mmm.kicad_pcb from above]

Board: 2 copper layers, 40.6 x 15.2 mm, 30 parts (0 on the bottom side), 13 nets, no tracks yet.

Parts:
C1, C2, C3, C4, C5, C6: 1000; SM0805
C7: 0.1; SM0805
D1, D2, D3, D4: SIL-2
D5: LED; LED-1206
P1, P2: CONN_4; PIN_ARRAY_4x1
R1, R2: 20k; SM0805
R3, R4, R5, R6: 10k; SM0805
R7, R8, R9, R10: 1k; SM0805
R11, R12: 470k; SM0805
R13, R14: 47k; SM0805
R15: 10 ohm; SM0805
U1: LM2903; so-8

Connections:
+5V: C7.1, P2.4, R9.2, R10.2, R13.1, R14.1, R15.2, U1.8
GND: C1.2, C2.2, C4.2, C6.2, C7.2, D5.2, P2.3, R7.1, R8.1, U1.4
unnamed: P2.2, R12.2, R14.2, U1.7
unnamed: D2.2, D4.1, R5.2, R12.1, U1.5
unnamed: D5.1, R15.1
unnamed: D2.1, D4.2, R6.2, R8.2, R10.1, U1.6
unnamed: C5.2, C6.1, P1.4, R2.2, R6.1
unnamed: C2.1, C5.1, P1.3, R2.1, R5.1
unnamed: D1.2, D3.1, R3.2, R11.1, U1.3
unnamed: D1.1, D3.2, R4.2, R7.2, R9.1, U1.2
unnamed: P2.1, R11.2, R13.2, U1.1
unnamed: C1.1, C3.1, P1.1, R1.1, R3.1
unnamed: C3.2, C4.1, P1.2, R1.2, R4.1
